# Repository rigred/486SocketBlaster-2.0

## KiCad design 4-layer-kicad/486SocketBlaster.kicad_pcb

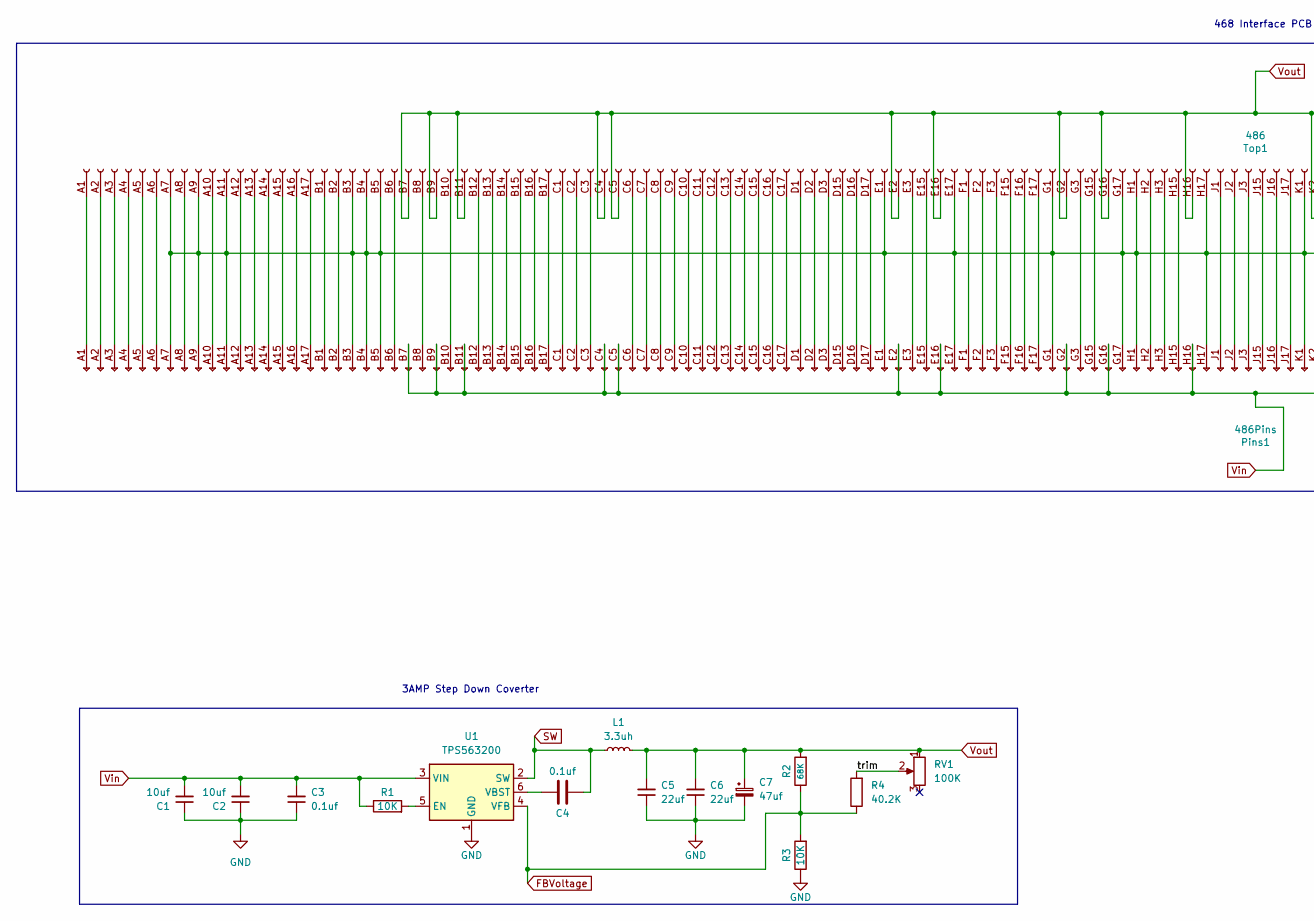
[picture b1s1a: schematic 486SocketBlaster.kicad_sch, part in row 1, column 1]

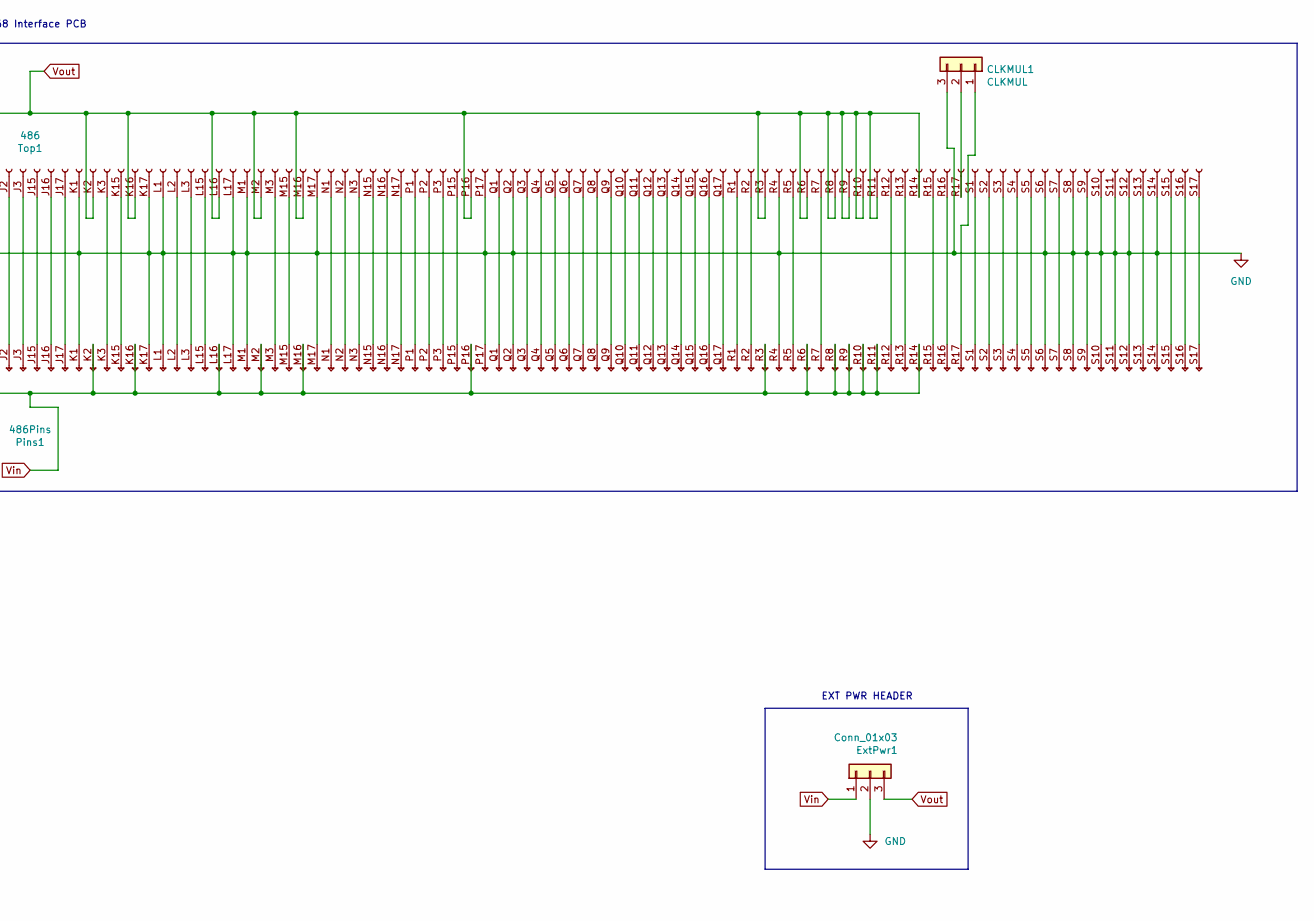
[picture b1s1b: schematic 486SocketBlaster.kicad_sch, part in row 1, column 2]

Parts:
C1, C2: 10uf; C_0805_2012Metric; JLCPCB C15850
C3, C4: 0.1uf; C_0603_1608Metric; JLCPCB C28233
C5, C6: 22uf; C_1206_3216Metric; JLCPCB C12891
C7: 47uf; CP_EIA-3216-12_Kemet-S_Pad1.58x1.35mm_HandSolder; JLCPCB C688949
CLKMUL1: CLKMUL; PinHeader_1x03_P2.54mm_Vertical
ExtPwr1: Conn_01x03; PinHeader_1x03_P2.54mm_Vertical
L1: 3.3uh; L_5.5x5.5; JLCPCB C436534
Pins1: 486Pins; 486_168pga_pins
R1, R3: 10K; R_0603_1608Metric; JLCPCB C25804
R2: 68K; R_0603_1608Metric; JLCPCB for set C4216
R4: 40.2K; R_0603_1608Metric; JLCPCB for ADJ C12447
RV1: 100K; tinySMDpot
Top1: 486; 486_168pga_socket
U1: TPS563200; SOT-23-6; LCSC C97253

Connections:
/trim: R4.2, RV1.2
FBVoltage: R2.1, R3.2, R4.1, U1.4 (VFB)
GND: C1.1, C2.1, C3.1, C5.1, C6.1, C7.2, CLKMUL1.3, ExtPwr1.2, Pins1.A7 (Pin_7), Pins1.A9 (Pin_9), Pins1.A11 (Pin_11), Pins1.B3 (Pin_3), Pins1.B4 (Pin_4), Pins1.B5 (Pin_5), Pins1.E1 (Pin_1), Pins1.E17 (Pin_17), Pins1.G1 (Pin_1), Pins1.G17 (Pin_17), Pins1.H1 (Pin_1), Pins1.H17 (Pin_17), Pins1.K1 (Pin_1), Pins1.K17 (Pin_17), Pins1.L1 (Pin_1), Pins1.L17 (Pin_17), Pins1.M1 (Pin_1), Pins1.M17 (Pin_17), Pins1.P17 (Pin_17), Pins1.Q2 (Pin_2), Pins1.R4 (Pin_4), Pins1.S6 (Pin_6), Pins1.S8 (Pin_8), Pins1.S9 (Pin_9), Pins1.S10 (Pin_10), Pins1.S11 (Pin_11), Pins1.S12 (Pin_12), Pins1.S14 (Pin_14), R3.1, Top1.A7 (Pin_7), Top1.A9 (Pin_9), Top1.A11 (Pin_11), Top1.B3 (Pin_3), Top1.B4 (Pin_4), Top1.B5 (Pin_5), Top1.E1 (Pin_1), Top1.E17 (Pin_17), Top1.G1 (Pin_1), Top1.G17 (Pin_17), Top1.H1 (Pin_1), Top1.H17 (Pin_17), Top1.K1 (Pin_1), Top1.K17 (Pin_17), Top1.L1 (Pin_1), Top1.L17 (Pin_17), Top1.M1 (Pin_1), Top1.M17 (Pin_17), Top1.P17 (Pin_17), Top1.Q2 (Pin_2), Top1.R4 (Pin_4), Top1.S6 (Pin_6), Top1.S8 (Pin_8), Top1.S9 (Pin_9), Top1.S10 (Pin_10), Top1.S11 (Pin_11), Top1.S12 (Pin_12), Top1.S14 (Pin_14), U1.1 (GND)
unnamed: C4.2, U1.6 (VBST)
unnamed: CLKMUL1.1, Pins1.R17 (Pin_17)
unnamed: CLKMUL1.2, Top1.R17 (Pin_17)
unnamed: Pins1.A1 (Pin_1), Top1.A1 (Pin_1)
unnamed: Pins1.A2 (Pin_2), Top1.A2 (Pin_2)
unnamed: Pins1.A3 (Pin_3), Top1.A3 (Pin_3)
unnamed: Pins1.A4 (Pin_4), Top1.A4 (Pin_4)
unnamed: Pins1.A5 (Pin_5), Top1.A5 (Pin_5)
unnamed: Pins1.A6 (Pin_6), Top1.A6 (Pin_6)
unnamed: Pins1.A8 (Pin_8), Top1.A8 (Pin_8)
unnamed: Pins1.A10 (Pin_10), Top1.A10 (Pin_10)
unnamed: Pins1.A12 (Pin_12), Top1.A12 (Pin_12)
unnamed: Pins1.A13 (Pin_13), Top1.A13 (Pin_13)
unnamed: Pins1.A14 (Pin_14), Top1.A14 (Pin_14)
unnamed: Pins1.A15 (Pin_15), Top1.A15 (Pin_15)
unnamed: Pins1.A16 (Pin_16), Top1.A16 (Pin_16)
unnamed: Pins1.A17 (Pin_17), Top1.A17 (Pin_17)
unnamed: Pins1.B1 (Pin_1), Top1.B1 (Pin_1)
unnamed: Pins1.B2 (Pin_2), Top1.B2 (Pin_2)
unnamed: Pins1.B6 (Pin_6), Top1.B6 (Pin_6)
unnamed: Pins1.B8 (Pin_8), Top1.B8 (Pin_8)
unnamed: Pins1.B10 (Pin_10), Top1.B10 (Pin_10)
unnamed: Pins1.B12 (Pin_12), Top1.B12 (Pin_12)
unnamed: Pins1.B13 (Pin_13), Top1.B13 (Pin_13)
unnamed: Pins1.B14 (Pin_14), Top1.B14 (Pin_14)
unnamed: Pins1.B15 (Pin_15), Top1.B15 (Pin_15)
unnamed: Pins1.B16 (Pin_16), Top1.B16 (Pin_16)
unnamed: Pins1.B17 (Pin_17), Top1.B17 (Pin_17)
unnamed: Pins1.C1 (Pin_1), Top1.C1 (Pin_1)
unnamed: Pins1.C2 (Pin_2), Top1.C2 (Pin_2)
unnamed: Pins1.C3 (Pin_3), Top1.C3 (Pin_3)
unnamed: Pins1.C6 (Pin_6), Top1.C6 (Pin_6)
unnamed: Pins1.C7 (Pin_7), Top1.C7 (Pin_7)
unnamed: Pins1.C8 (Pin_8), Top1.C8 (Pin_8)
unnamed: Pins1.C9 (Pin_9), Top1.C9 (Pin_9)
unnamed: Pins1.C10 (Pin_10), Top1.C10 (Pin_10)
unnamed: Pins1.C11 (Pin_11), Top1.C11 (Pin_11)
unnamed: Pins1.C12 (Pin_12), Top1.C12 (Pin_12)
unnamed: Pins1.C13 (Pin_13), Top1.C13 (Pin_13)
unnamed: Pins1.C14 (Pin_14), Top1.C14 (Pin_14)
unnamed: Pins1.C15 (Pin_15), Top1.C15 (Pin_15)
unnamed: Pins1.C16 (Pin_16), Top1.C16 (Pin_16)
unnamed: Pins1.C17 (Pin_17), Top1.C17 (Pin_17)
unnamed: Pins1.D1 (Pin_1), Top1.D1 (Pin_1)
unnamed: Pins1.D2 (Pin_2), Top1.D2 (Pin_2)
unnamed: Pins1.D3 (Pin_3), Top1.D3 (Pin_3)
unnamed: Pins1.D15 (Pin_15), Top1.D15 (Pin_15)
unnamed: Pins1.D16 (Pin_16), Top1.D16 (Pin_16)
unnamed: Pins1.D17 (Pin_17), Top1.D17 (Pin_17)
unnamed: Pins1.E3 (Pin_3), Top1.E3 (Pin_3)
unnamed: Pins1.E15 (Pin_15), Top1.E15 (Pin_15)
unnamed: Pins1.F1 (Pin_1), Top1.F1 (Pin_1)
unnamed: Pins1.F2 (Pin_2), Top1.F2 (Pin_2)
unnamed: Pins1.F3 (Pin_3), Top1.F3 (Pin_3)
unnamed: Pins1.F15 (Pin_15), Top1.F15 (Pin_15)
unnamed: Pins1.F16 (Pin_16), Top1.F16 (Pin_16)
unnamed: Pins1.F17 (Pin_17), Top1.F17 (Pin_17)
unnamed: Pins1.G3 (Pin_3), Top1.G3 (Pin_3)
unnamed: Pins1.G15 (Pin_15), Top1.G15 (Pin_15)
unnamed: Pins1.H2 (Pin_2), Top1.H2 (Pin_2)
unnamed: Pins1.H3 (Pin_3), Top1.H3 (Pin_3)
unnamed: Pins1.H15 (Pin_15), Top1.H15 (Pin_15)
unnamed: Pins1.J1 (Pin_1), Top1.J1 (Pin_1)
unnamed: Pins1.J2 (Pin_2), Top1.J2 (Pin_2)
unnamed: Pins1.J3 (Pin_3), Top1.J3 (Pin_3)
unnamed: Pins1.J15 (Pin_15), Top1.J15 (Pin_15)
unnamed: Pins1.J16 (Pin_16), Top1.J16 (Pin_16)
unnamed: Pins1.J17 (Pin_17), Top1.J17 (Pin_17)
unnamed: Pins1.K3 (Pin_3), Top1.K3 (Pin_3)
unnamed: Pins1.K15 (Pin_15), Top1.K15 (Pin_15)
unnamed: Pins1.L2 (Pin_2), Top1.L2 (Pin_2)
unnamed: Pins1.L3 (Pin_3), Top1.L3 (Pin_3)
unnamed: Pins1.L15 (Pin_15), Top1.L15 (Pin_15)
unnamed: Pins1.M3 (Pin_3), Top1.M3 (Pin_3)
unnamed: Pins1.M15 (Pin_15), Top1.M15 (Pin_15)
unnamed: Pins1.N1 (Pin_1), Top1.N1 (Pin_1)
unnamed: Pins1.N2 (Pin_2), Top1.N2 (Pin_2)
unnamed: Pins1.N3 (Pin_3), Top1.N3 (Pin_3)
unnamed: Pins1.N15 (Pin_15), Top1.N15 (Pin_15)
unnamed: Pins1.N16 (Pin_16), Top1.N16 (Pin_16)
unnamed: Pins1.N17 (Pin_17), Top1.N17 (Pin_17)
unnamed: Pins1.P1 (Pin_1), Top1.P1 (Pin_1)
unnamed: Pins1.P2 (Pin_2), Top1.P2 (Pin_2)
unnamed: Pins1.P3 (Pin_3), Top1.P3 (Pin_3)
unnamed: Pins1.P15 (Pin_15), Top1.P15 (Pin_15)
unnamed: Pins1.Q1 (Pin_1), Top1.Q1 (Pin_1)
unnamed: Pins1.Q3 (Pin_3), Top1.Q3 (Pin_3)
unnamed: Pins1.Q4 (Pin_4), Top1.Q4 (Pin_4)
unnamed: Pins1.Q5 (Pin_5), Top1.Q5 (Pin_5)
unnamed: Pins1.Q6 (Pin_6), Top1.Q6 (Pin_6)
unnamed: Pins1.Q7 (Pin_7), Top1.Q7 (Pin_7)
unnamed: Pins1.Q8 (Pin_8), Top1.Q8 (Pin_8)
unnamed: Pins1.Q9 (Pin_9), Top1.Q9 (Pin_9)
unnamed: Pins1.Q10 (Pin_10), Top1.Q10 (Pin_10)
unnamed: Pins1.Q11 (Pin_11), Top1.Q11 (Pin_11)
unnamed: Pins1.Q12 (Pin_12), Top1.Q12 (Pin_12)
unnamed: Pins1.Q13 (Pin_13), Top1.Q13 (Pin_13)
unnamed: Pins1.Q14 (Pin_14), Top1.Q14 (Pin_14)
unnamed: Pins1.Q15 (Pin_15), Top1.Q15 (Pin_15)
unnamed: Pins1.Q16 (Pin_16), Top1.Q16 (Pin_16)
unnamed: Pins1.Q17 (Pin_17), Top1.Q17 (Pin_17)
unnamed: Pins1.R1 (Pin_1), Top1.R1 (Pin_1)
unnamed: Pins1.R2 (Pin_2), Top1.R2 (Pin_2)
unnamed: Pins1.R5 (Pin_5), Top1.R5 (Pin_5)
unnamed: Pins1.R7 (Pin_7), Top1.R7 (Pin_7)
unnamed: Pins1.R12 (Pin_12), Top1.R12 (Pin_12)
unnamed: Pins1.R13 (Pin_13), Top1.R13 (Pin_13)
unnamed: Pins1.R15 (Pin_15), Top1.R15 (Pin_15)
unnamed: Pins1.R16 (Pin_16), Top1.R16 (Pin_16)
unnamed: Pins1.S1 (Pin_1), Top1.S1 (Pin_1)
unnamed: Pins1.S2 (Pin_2), Top1.S2 (Pin_2)
unnamed: Pins1.S3 (Pin_3), Top1.S3 (Pin_3)
unnamed: Pins1.S4 (Pin_4), Top1.S4 (Pin_4)
unnamed: Pins1.S5 (Pin_5), Top1.S5 (Pin_5)
unnamed: Pins1.S7 (Pin_7), Top1.S7 (Pin_7)
unnamed: Pins1.S13 (Pin_13), Top1.S13 (Pin_13)
unnamed: Pins1.S15 (Pin_15), Top1.S15 (Pin_15)
unnamed: Pins1.S16 (Pin_16), Top1.S16 (Pin_16)
unnamed: Pins1.S17 (Pin_17), Top1.S17 (Pin_17)
unnamed: R1.2, U1.5 (EN)
SW: C4.1, L1.1, U1.2 (SW)
Vin: C1.2, C2.2, C3.2, ExtPwr1.1, Pins1.B7 (Pin_7), Pins1.B9 (Pin_9), Pins1.B11 (Pin_11), Pins1.C4 (Pin_4), Pins1.C5 (Pin_5), Pins1.E2 (Pin_2), Pins1.E16 (Pin_16), Pins1.G2 (Pin_2), Pins1.G16 (Pin_16), Pins1.H16 (Pin_16), Pins1.K2 (Pin_2), Pins1.K16 (Pin_16), Pins1.L16 (Pin_16), Pins1.M2 (Pin_2), Pins1.M16 (Pin_16), Pins1.P16 (Pin_16), Pins1.R3 (Pin_3), Pins1.R6 (Pin_6), Pins1.R8 (Pin_8), Pins1.R9 (Pin_9), Pins1.R10 (Pin_10), Pins1.R11 (Pin_11), Pins1.R14 (Pin_14), R1.1, U1.3 (VIN)
Vout: C5.2, C6.2, C7.1, ExtPwr1.3, L1.2, R2.2, RV1.1, Top1.B7 (Pin_7), Top1.B9 (Pin_9), Top1.B11 (Pin_11), Top1.C4 (Pin_4), Top1.C5 (Pin_5), Top1.E2 (Pin_2), Top1.E16 (Pin_16), Top1.G2 (Pin_2), Top1.G16 (Pin_16), Top1.H16 (Pin_16), Top1.K2 (Pin_2), Top1.K16 (Pin_16), Top1.L16 (Pin_16), Top1.M2 (Pin_2), Top1.M16 (Pin_16), Top1.P16 (Pin_16), Top1.R3 (Pin_3), Top1.R6 (Pin_6), Top1.R8 (Pin_8), Top1.R9 (Pin_9), Top1.R10 (Pin_10), Top1.R11 (Pin_11), Top1.R14 (Pin_14)

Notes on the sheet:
468 Interface PCB
EXT PWR HEADER
3AMP Step Down Coverter

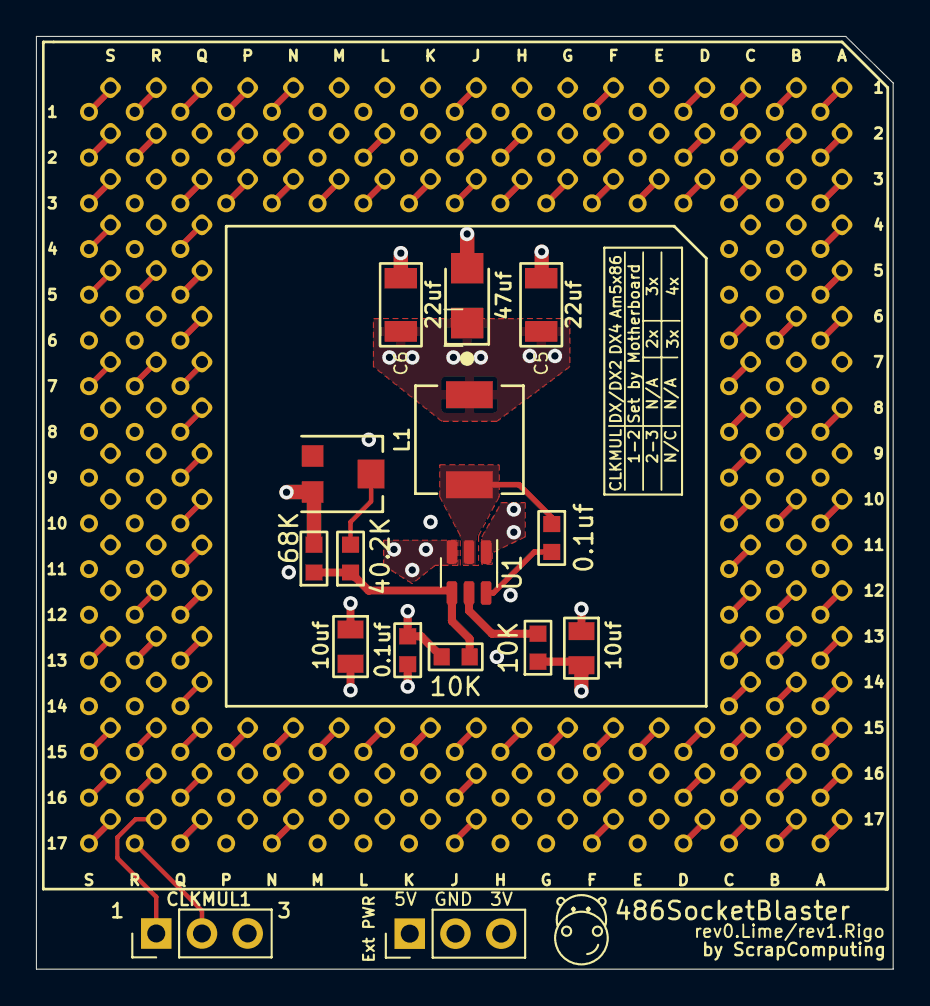
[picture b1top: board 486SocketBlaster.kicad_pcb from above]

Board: 4 copper layers, 47.6 x 51.8 mm, 18 parts (0 on the bottom side), 126 nets.

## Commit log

2023-02-05 Add new 486 Regulator design with redone 4 Layer PCB Thanks to LimeProgramming(CalamityLime) for the original inspiration
